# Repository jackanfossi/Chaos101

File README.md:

#  Chaos 101

Welcome to **Chaos 101**, an interactive project developed at **Grenoble INP - Phelma** to bridge the gap between abstract mathematics and physical reality.

We provide a tangible educational experience to explore how deterministic rules can lead to completely unpredictable behavior. Through our custom electronic circuit and Wi-Fi visualization system, you can discover the **"order hidden behind chaos"** and its vital role in modern technologies like secure data encryption.

---

## 🌀 Chaos for Everyone: An Intuitive Introduction
If you are new to this topic, here is a simple way to understand what we are working on:

### 1. Deterministic but Unpredictable
Usually, we think the world is either **predictable**, like planetary orbits, or **random**, like thermal fluctuations. Chaos is a special third category: it follows precise rules (it is deterministic), yet it turns out to be completely unpredictable over the long term.

### 2. The Butterfly Effect
The core of chaos is **extreme sensitivity to initial conditions**. If two identical chaotic systems start from states that differ by only a microscopic margin, their trajectories will eventually yield completely different outputs. This is why even a tiny change can lead to a massive difference later on.

### 3. Why is it useful? (TRNG)
Because chaos is so sensitive and unpredictable, it is perfect for creating **True Random Numbers**. While computers usually use predictable algorithms to create "random" numbers, our circuit uses the physical "messiness" of chaos to create sequences that are mathematically impossible to predict with precision. This makes digital encryption and cybersecurity much safer.

## 📂 Project Overview: What you will find
Based on our technical specifications, this repository provides a functional educational package that includes a real working device and the associated documentation. The goal is to provide an intuitive and visual comprehension of a chaotic system through an electronic circuit.

In this project, you will find:
* **Tangible Educational Device:** A portable and interactive hardware station designed for the general public.
* **Visualization System:** Direct monitoring of the system's evolution and display of the characteristic phase space diagrams, called attractors.
* **Wireless Communication:** A microcontroller interface using Wi-Fi protocol to allow for a simple setup and smartphone connection.
* **Practical Application (TRNG):** A demo of a True Random Number Generator to showcase the relevance of chaos theory in technology and security.
* **Autonomous Power Supply:** The entire system features an autonomous power supply to ensure maximum portability for events.
* **Open-Source Access:** Full technical documentation and a guide to set up the experience autonomously.
### Functional Diagram

---

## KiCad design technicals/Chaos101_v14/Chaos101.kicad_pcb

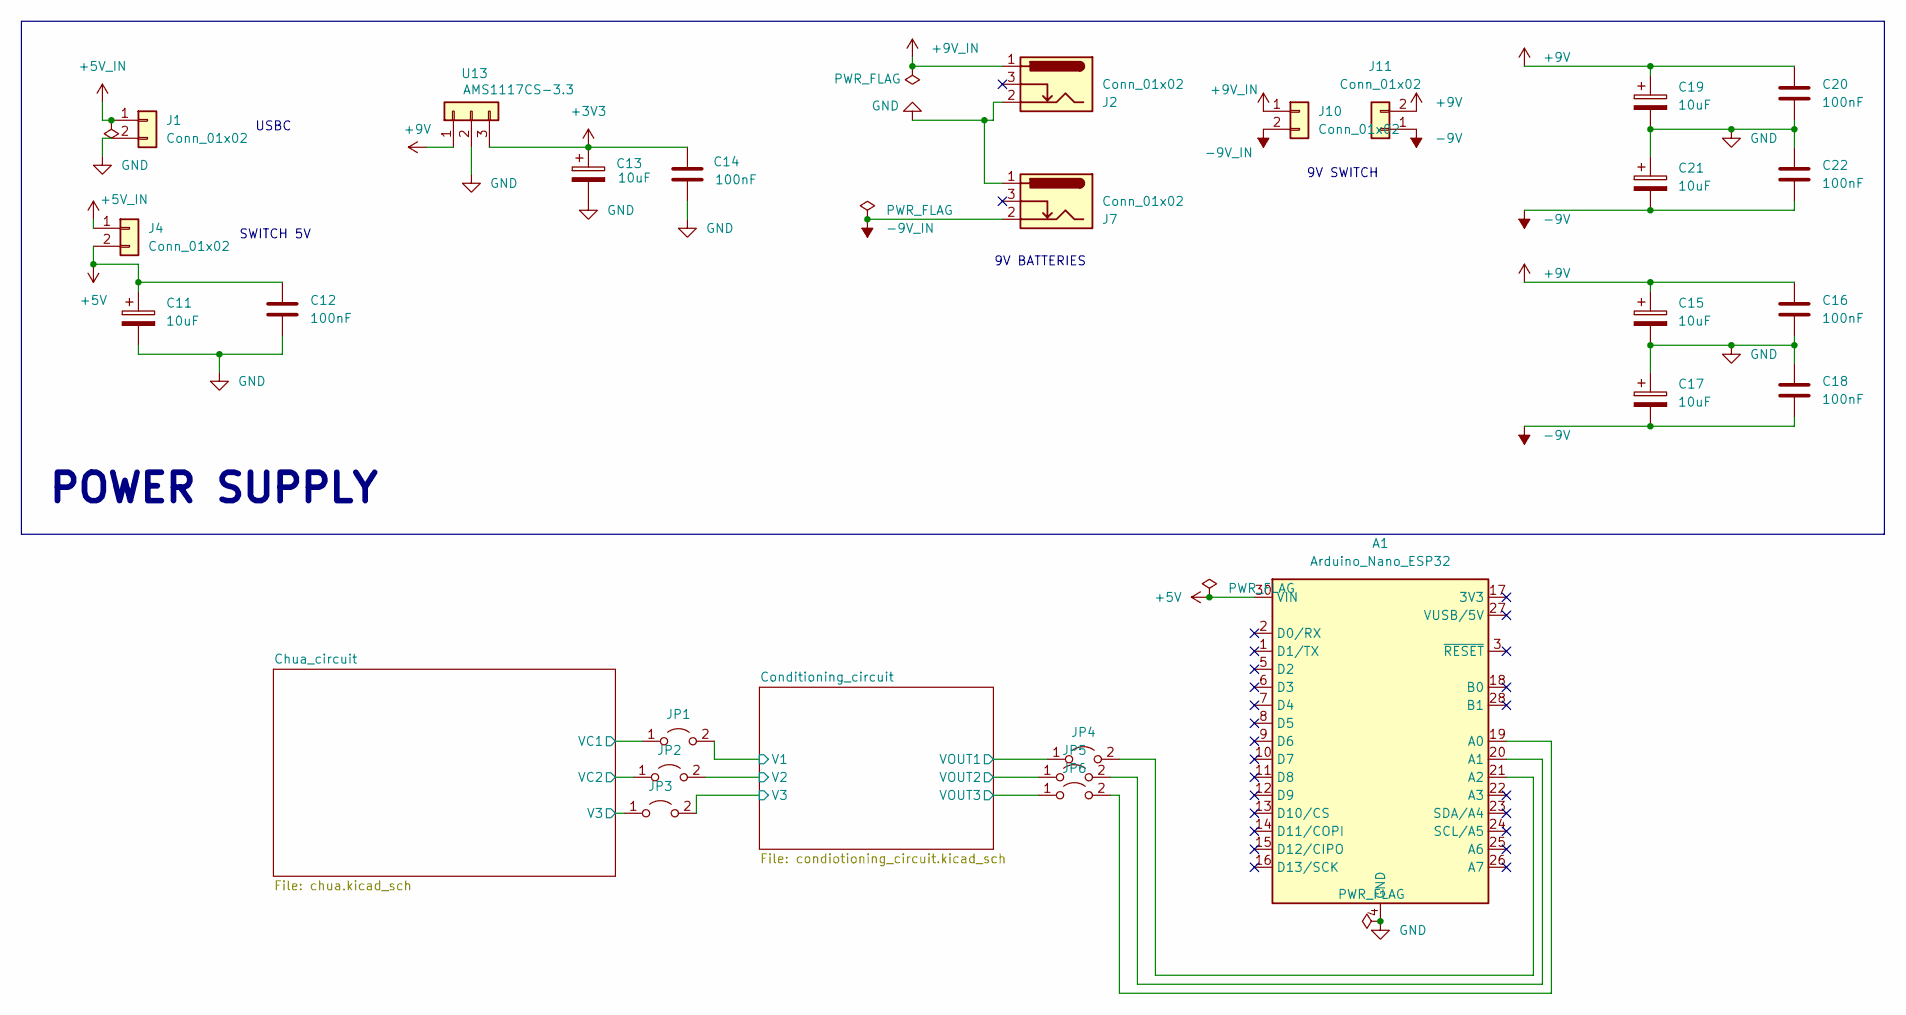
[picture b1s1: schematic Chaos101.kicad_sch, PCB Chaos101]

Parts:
A1: Arduino_Nano_ESP32; Arduino_Nano
C11, C13, C15, C17, C19, C21: 10uF; CONDENSATEUR_POL_5.08MM
C12, C14, C16, C18, C20, C22: 100nF; CONDENSATEUR_5.08MM
J1, J4, J10, J11: Conn_01x02; PinHeader_1x02_P2.54mm_Vertical
J2, J7: Conn_01x02; BarrelJack_CLIFF_FC681465S_SMT_Horizontal
JP1, JP2, JP3, JP4, JP5, JP6: r=1m; PinHeader_1x02_P2.54mm_Vertical
U13: AMS1117CS-3.3; PinHeader_1x03_P2.54mm_Vertical

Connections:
+3V3: C13.1, C14.1, U13.3; also elsewhere on the board
+5V: A1.30 (VIN), C11.1, C12.1, J4.2
+5V_IN: J1.1, J4.1
+9V: C15.1, C16.1, C19.1, C20.1, J11.2, U13.1; also elsewhere on the board
+9V_IN: J2.1, J10.1
-9V: C17.2, C18.2, C21.2, C22.2, J11.1; also elsewhere on the board
-9V_IN: J7.2, J10.2
/Chua_circuit/V3: JP3.1 (A); also elsewhere on the board
/Chua_circuit/VC1: JP1.1 (A); also elsewhere on the board
/Chua_circuit/VC2: JP2.1 (A); also elsewhere on the board
/Conditioning_circuit/V1: JP1.2 (B); also elsewhere on the board
/Conditioning_circuit/V2: JP2.2 (B); also elsewhere on the board
/Conditioning_circuit/V3: JP3.2 (B); also elsewhere on the board
/Conditioning_circuit/VOUT1: JP4.1 (A); also elsewhere on the board
/Conditioning_circuit/VOUT2: JP5.1 (A); also elsewhere on the board
/Conditioning_circuit/VOUT3: JP6.1 (A); also elsewhere on the board
GND: A1.4 (GND), A1.29 (GND), C11.2, C12.2, C13.2, C14.2, C15.2, C16.2, C17.1, C18.1, C19.2, C20.2, C21.1, C22.1, J1.2, J2.2, J7.1, U13.2; also elsewhere on the board
unnamed: A1.19 (A0), JP6.2 (B)
unnamed: A1.20 (A1), JP5.2 (B)
unnamed: A1.21 (A2), JP4.2 (B)

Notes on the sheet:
9V SWITCH
9V BATTERIES
POWER SUPPLY
USBC
SWITCH 5V

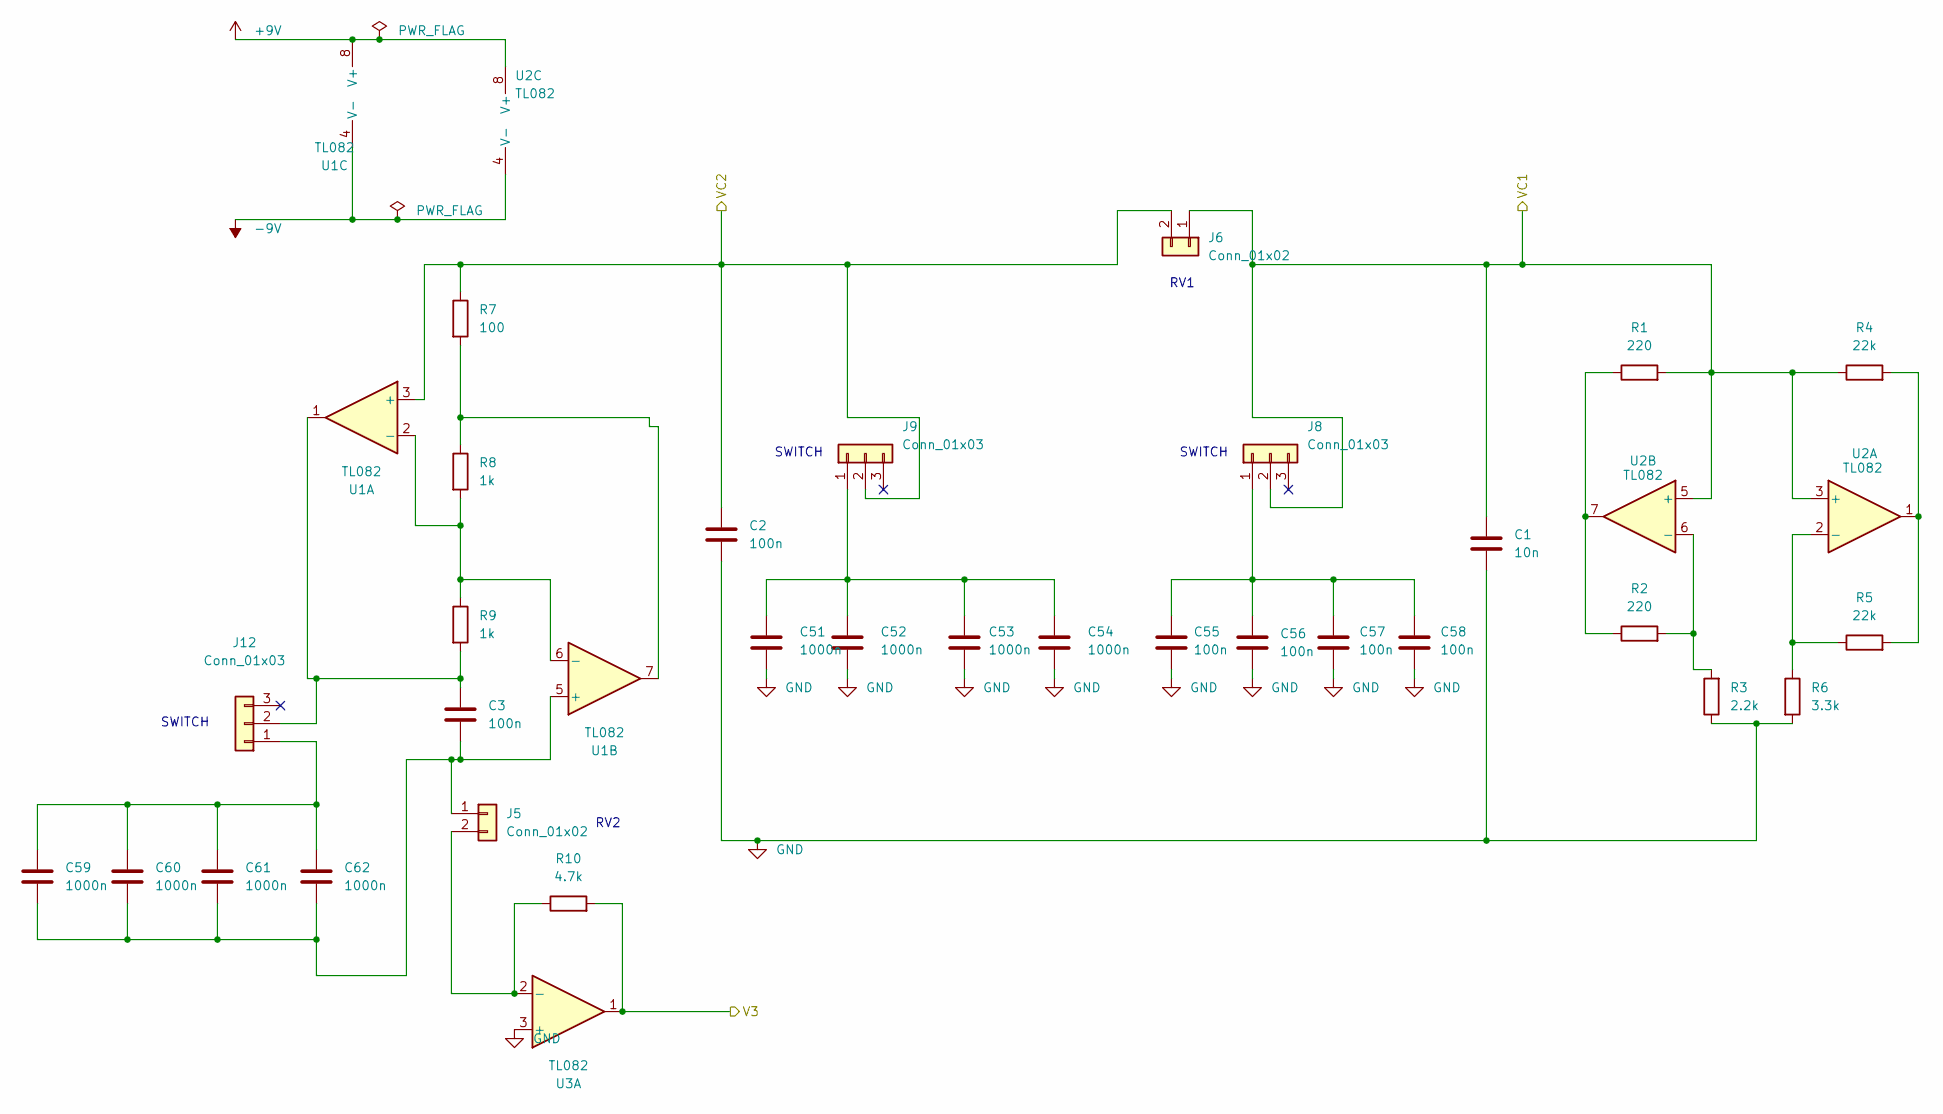
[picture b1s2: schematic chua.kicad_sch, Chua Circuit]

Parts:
C1: 10n; CONDENSATEUR_5.08MM
C2, C3, C55, C56, C57, C58: 100n; CONDENSATEUR_5.08MM
C51, C52, C53, C54, C59, C60, C61, C62: 1000n; CONDENSATEUR_5.08MM
J5, J6: Conn_01x02; PinHeader_1x02_P2.54mm_Vertical
J8, J9, J12: Conn_01x03; PinHeader_1x03_P2.54mm_Vertical
R1, R2: 220; R_Axial_DIN0207_L6.3mm_D2.5mm_P10.16mm_Horizontal
R3: 2.2k; R_Axial_DIN0207_L6.3mm_D2.5mm_P10.16mm_Horizontal
R4, R5: 22k; R_Axial_DIN0207_L6.3mm_D2.5mm_P10.16mm_Horizontal
R6: 3.3k; R_Axial_DIN0207_L6.3mm_D2.5mm_P10.16mm_Horizontal
R7: 100; R_Axial_DIN0207_L6.3mm_D2.5mm_P10.16mm_Horizontal
R8, R9: 1k; R_Axial_DIN0207_L6.3mm_D2.5mm_P10.16mm_Horizontal
R10: 4.7k; R_Axial_DIN0207_L6.3mm_D2.5mm_P10.16mm_Horizontal
U1, U2, U3: TL082; DIP-8_W7.62mm_Socket_LongPads

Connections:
+9V: U1.8 (V+), U2.8 (V+); also elsewhere on the board
-9V: U1.4 (V-), U2.4 (V-); also elsewhere on the board
/Chua_circuit/V3: R10.2, U3.1; also elsewhere on the board
/Chua_circuit/VC1: C1.1, J6.1, J8.2, R1.2, R4.1, U2.3 (+), U2.5 (+); also elsewhere on the board
/Chua_circuit/VC2: C2.1, J6.2, J9.2, R7.1, U1.3 (+); also elsewhere on the board
GND: C1.2, C2.2, C51.2, C52.2, C53.2, C54.2, C55.2, C56.2, C57.2, C58.2, R3.1, R6.2, U3.3 (+); also elsewhere on the board
unnamed: C3.2, C59.2, C60.2, C61.2, C62.2, J5.1, U1.5 (+)
unnamed: J5.2, R10.1, U3.2 (-)
unnamed: C55.1, C56.1, C57.1, C58.1, J8.1
unnamed: C51.1, C52.1, C53.1, C54.1, J9.1
unnamed: C59.1, C60.1, C61.1, C62.1, J12.1
unnamed: C3.1, J12.2, R9.2, U1.1
unnamed: R1.1, R2.1, U2.7
unnamed: R4.2, R5.2, U2.1
unnamed: R7.2, R8.1, U1.7
unnamed: R8.2, R9.1, U1.2 (-), U1.6 (-)
unnamed: R5.1, R6.1, U2.2 (-)
unnamed: R2.2, R3.2, U2.6 (-)

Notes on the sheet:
RV2
SWITCH
RV1

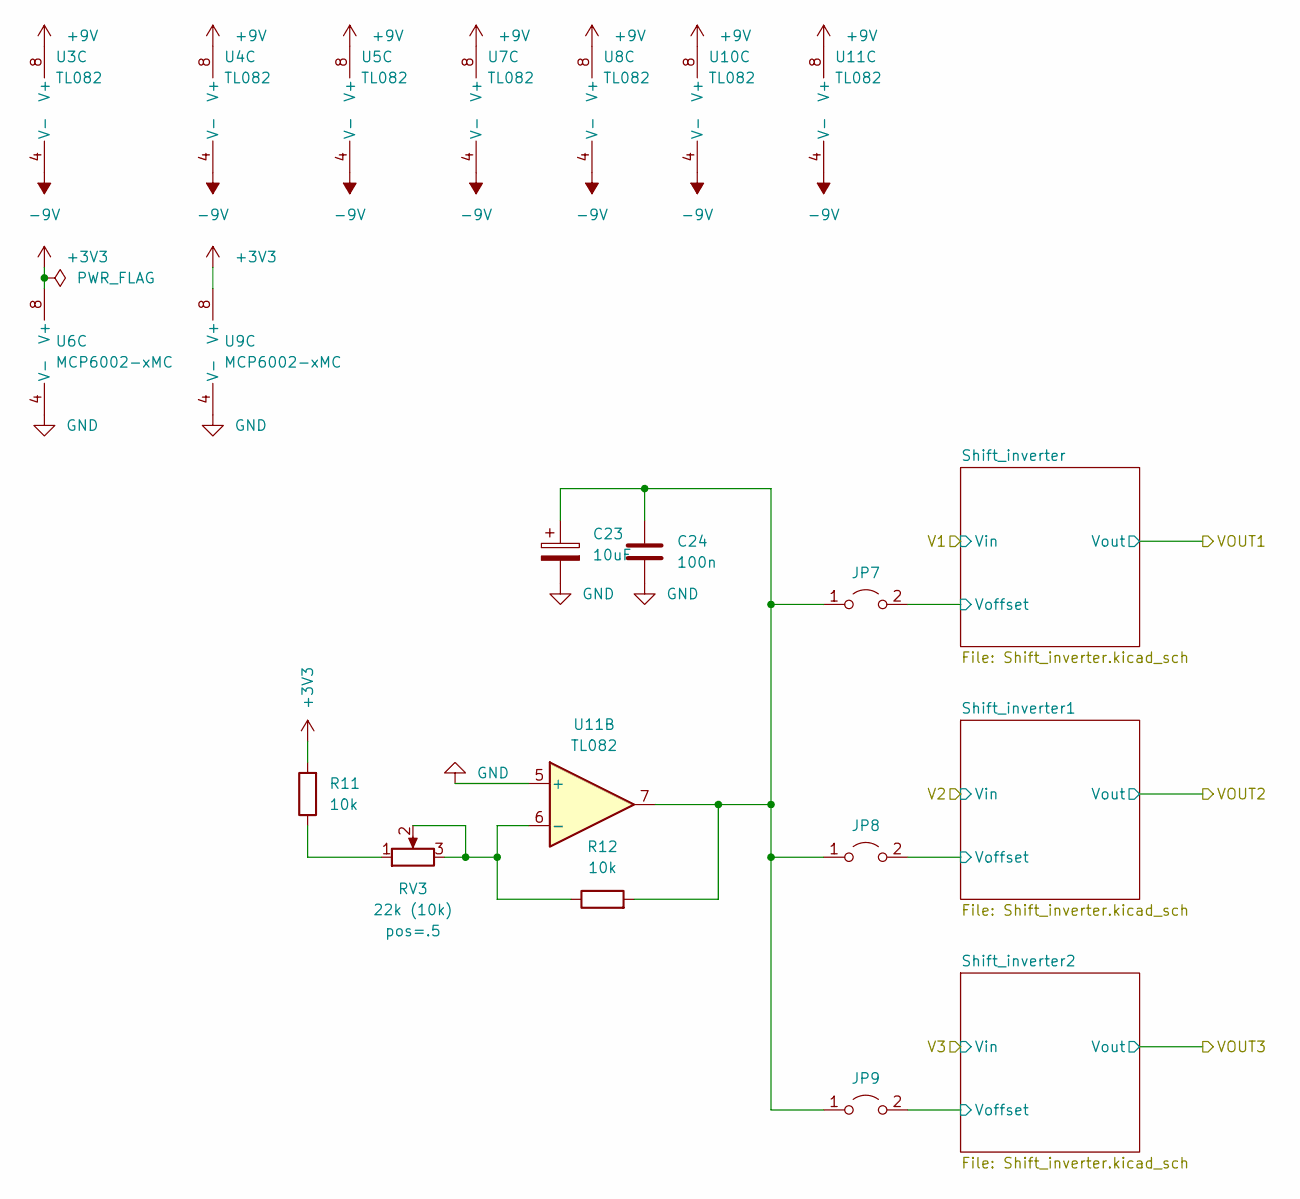
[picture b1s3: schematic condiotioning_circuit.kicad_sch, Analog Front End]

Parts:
C23: 10uF; CONDENSATEUR_POL_5.08MM
C24: 100n; CONDENSATEUR_5.08MM
JP7, JP8, JP9: r=1m; PinHeader_1x02_P2.54mm_Vertical
R11, R12: 10k; R_Axial_DIN0207_L6.3mm_D2.5mm_P10.16mm_Horizontal
RV3: 22k (10k); Potentiometer_Piher_PT-10-V10_Vertical
U3, U4, U5, U7, U8, U10, U11: TL082; DIP-8_W7.62mm_Socket_LongPads
U6, U9: MCP6002-xMC; DIP-8_W7.62mm_Socket_LongPads

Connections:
+3V3: R11.2, U6.8 (V+), U9.8 (V+); also elsewhere on the board
+9V: U3.8 (V+), U4.8 (V+), U5.8 (V+), U7.8 (V+), U8.8 (V+), U10.8 (V+), U11.8 (V+); also elsewhere on the board
-9V: U3.4 (V-), U4.4 (V-), U5.4 (V-), U7.4 (V-), U8.4 (V-), U10.4 (V-), U11.4 (V-); also elsewhere on the board
/Conditioning_circuit/Shift_inverter1/Voffset: JP8.2 (B); also elsewhere on the board
/Conditioning_circuit/Shift_inverter2/Voffset: JP9.2 (B); also elsewhere on the board
/Conditioning_circuit/Shift_inverter/Voffset: JP7.2 (B); also elsewhere on the board
/Conditioning_circuit/V2: U5.5 (+); also elsewhere on the board
/Conditioning_circuit/VOUT2: U6.6 (-), U6.7; also elsewhere on the board
GND: C23.2, C24.2, U6.4 (V-), U9.4 (V-), U11.5 (+); also elsewhere on the board
unnamed 24: U6.5 (+); also elsewhere on the board
unnamed: C23.1, C24.1, JP7.1 (A), JP8.1 (A), JP9.1 (A), R12.2, U11.7
unnamed: R11.1, RV3.1
unnamed 47: U5.6 (-), U5.7; also elsewhere on the board
unnamed: R12.1, RV3.2, RV3.3, U11.6 (-)

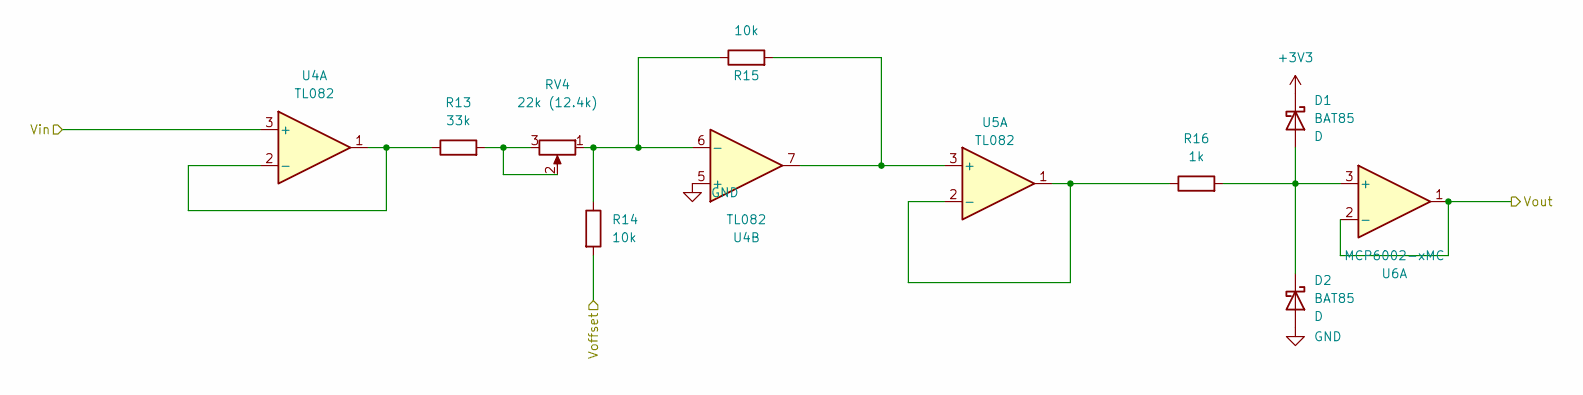
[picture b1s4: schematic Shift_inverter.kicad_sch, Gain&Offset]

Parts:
D1, D2: BAT85; DIODE_10.16mm
R13: 33k; R_Axial_DIN0207_L6.3mm_D2.5mm_P10.16mm_Horizontal
R14, R15: 10k; R_Axial_DIN0207_L6.3mm_D2.5mm_P10.16mm_Horizontal
R16: 1k; R_Axial_DIN0207_L6.3mm_D2.5mm_P10.16mm_Horizontal
RV4: 22k (12.4k); Potentiometer_Piher_PT-10-V10_Vertical
U4, U5: TL082; DIP-8_W7.62mm_Socket_LongPads
U6: MCP6002-xMC; DIP-8_W7.62mm_Socket_LongPads

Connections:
+3V3: D1.1 (K); also elsewhere on the board
/Conditioning_circuit/Shift_inverter/Voffset: R14.2; also elsewhere on the board
/Conditioning_circuit/V1: U4.3 (+); also elsewhere on the board
/Conditioning_circuit/V2: U5.5 (+); also elsewhere on the board
/Conditioning_circuit/VOUT1: U6.1, U6.2 (-); also elsewhere on the board
/Conditioning_circuit/VOUT2: U6.6 (-), U6.7; also elsewhere on the board
GND: D2.2 (A), U4.5 (+); also elsewhere on the board
unnamed: D1.2 (A), D2.1 (K), R16.2, U6.3 (+)
unnamed 24: U6.5 (+); also elsewhere on the board
unnamed: R13.2, RV4.2, RV4.3
unnamed: R13.1, U4.1, U4.2 (-)
unnamed: R14.1, R15.1, RV4.1, U4.6 (-)
unnamed: R15.2, U4.7, U5.3 (+)
unnamed: R16.1, U5.1, U5.2 (-)
unnamed 47: U5.6 (-), U5.7; also elsewhere on the board

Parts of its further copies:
D3, D4, D5, D6: BAT85; DIODE_10.16mm
R17, R21: 33k; R_Axial_DIN0207_L6.3mm_D2.5mm_P10.16mm_Horizontal
R18, R19, R22, R23: 10k; R_Axial_DIN0207_L6.3mm_D2.5mm_P10.16mm_Horizontal
R20, R24: 1k; R_Axial_DIN0207_L6.3mm_D2.5mm_P10.16mm_Horizontal
RV5, RV6: 22k (12.4k); Potentiometer_Piher_PT-10-V10_Vertical

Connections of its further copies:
+3V3: D3.1 (K), D5.1 (K); also elsewhere on the board
/Conditioning_circuit/Shift_inverter1/Voffset: R18.2; also elsewhere on the board
/Conditioning_circuit/Shift_inverter2/Voffset: R22.2; also elsewhere on the board
GND: D4.2 (A), D6.2 (A); also elsewhere on the board
unnamed 24: D3.2 (A), D4.1 (K), R20.2; also elsewhere on the board
unnamed 25: D5.2 (A), D6.1 (K), R24.2; also elsewhere on the board
unnamed: R17.2, RV5.2, RV5.3
unnamed: R21.2, RV6.2, RV6.3
unnamed 47: R17.1; also elsewhere on the board
unnamed 48: R18.1, R19.1, RV5.1; also elsewhere on the board
unnamed 49: R19.2; also elsewhere on the board
unnamed 50: R20.1; also elsewhere on the board
unnamed 51: R21.1; also elsewhere on the board
unnamed 52: R22.1, R23.1, RV6.1; also elsewhere on the board
unnamed 53: R23.2; also elsewhere on the board
unnamed 54: R24.1; also elsewhere on the board

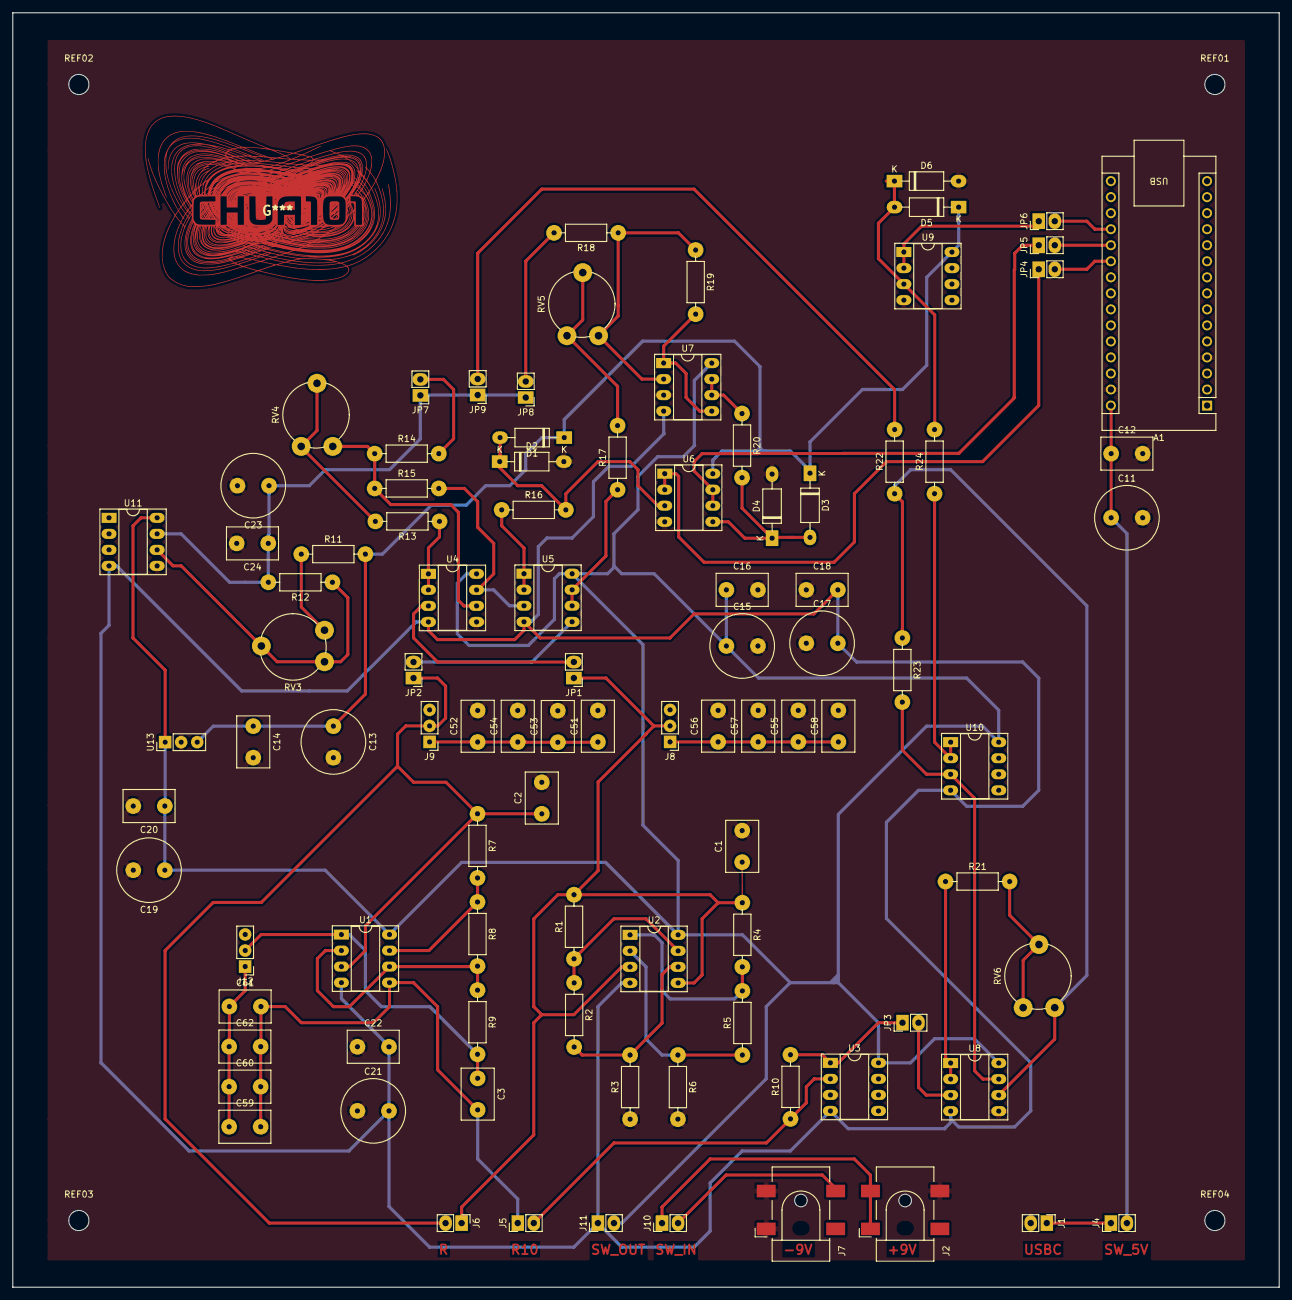
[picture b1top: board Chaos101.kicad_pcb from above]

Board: 2 copper layers, 200.7 x 201.9 mm, 100 parts (0 on the bottom side), 56 nets.

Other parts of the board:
REF01, REF02, REF03, REF04: MountingHole_3.2mm_M3

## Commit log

2026-04-15 initial structure
2026-04-15 add intro
2026-04-15 logo
2026-04-15 modifiche
2026-04-15 logo2
2026-04-15 ultime
2026-05-14 add report
2026-05-17 aggiorna
2026-05-17 elimino
2026-05-17 activity
2026-05-19 final_report
2026-05-19 codes
2026-05-19 matlab_simulations
2026-05-19 Main_interface
2026-05-20 folders
2026-05-21 Add MIT License to the project
